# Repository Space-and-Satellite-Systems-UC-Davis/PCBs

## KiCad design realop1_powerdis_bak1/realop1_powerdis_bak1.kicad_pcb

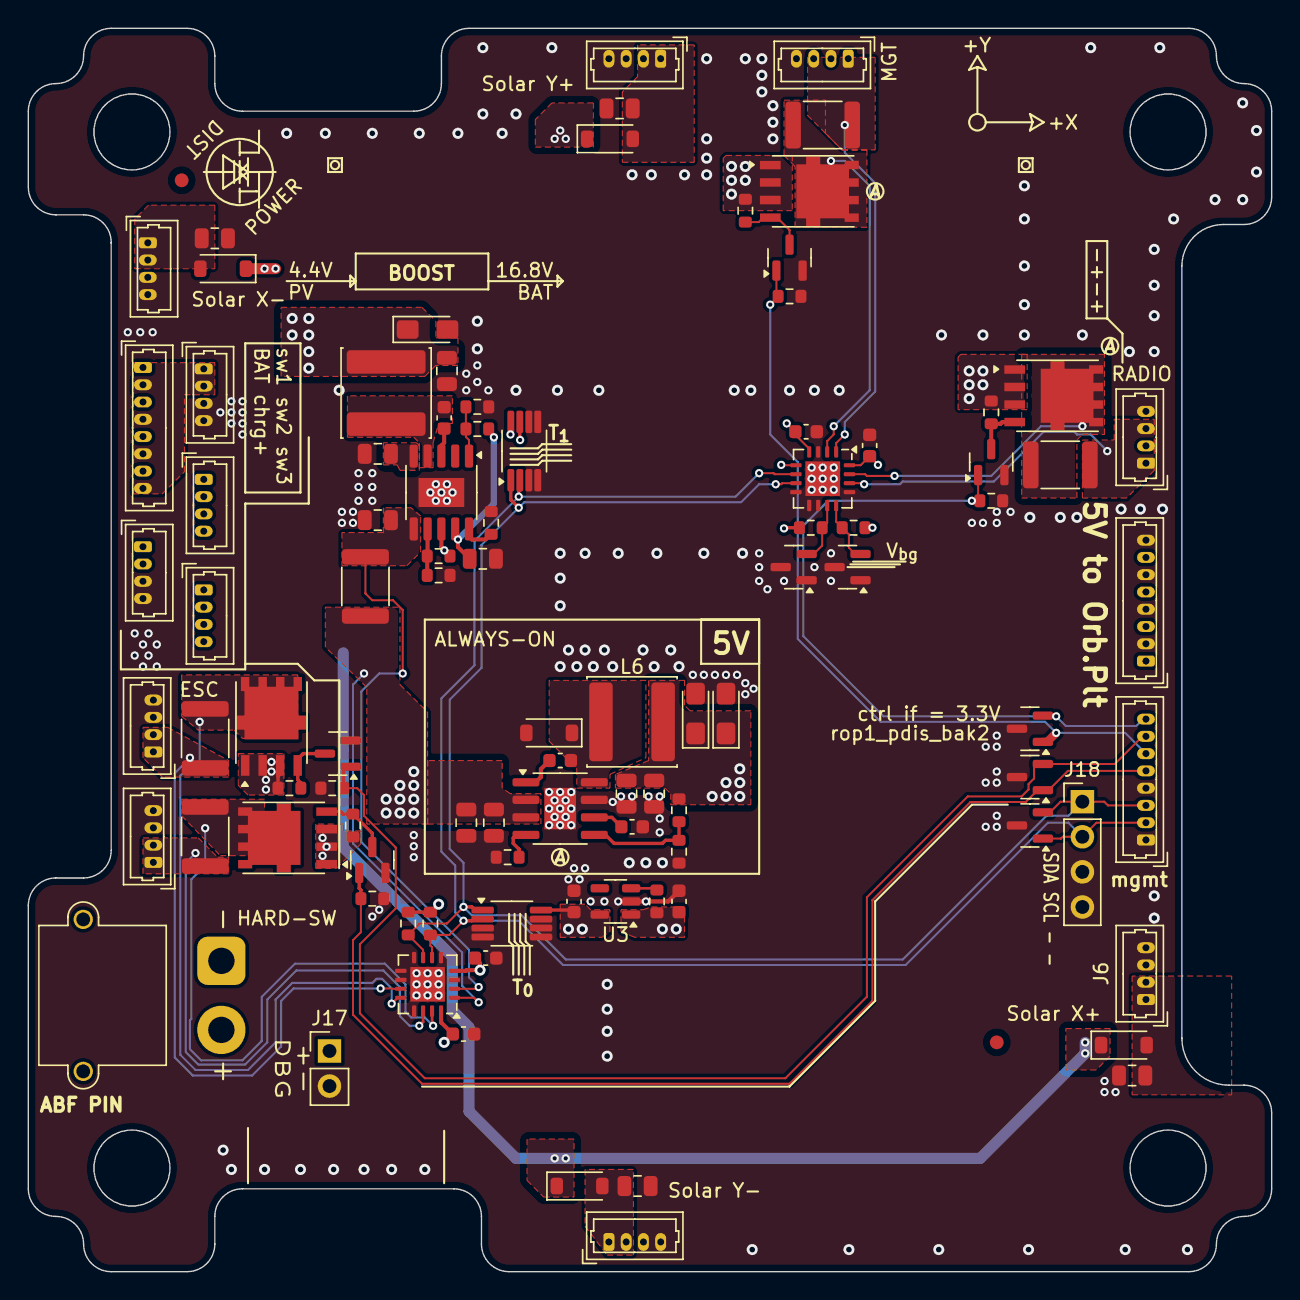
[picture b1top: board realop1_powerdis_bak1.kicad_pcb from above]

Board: 4 copper layers, 90.0 x 90.0 mm, 97 parts (0 on the bottom side), 47 nets.

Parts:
C1, C2, C3, C4, C14, C15, C16, C17, C25, C26, C29, C30: 10uF; C_0805_2012Metric
C5, C6, C18: 47uF A; CP_EIA-3216-18_Kemet-A_Pad1.58x1.35mm_HandSolder
C7, C8, C9, C10, C11, C12, C13, C28: 1uF; C_0603_1608Metric
C27: 10nF; C_0603_1608Metric
D1, D2, D3, D4, D5: 1n5819hw; D_SOD-123
D6, D7, D8: SM712_SOT23; SOT-23
FID1, FID2: Fiducial; Fiducial_1mm_Mask2mm
J1: mnt_fltctrl; Molex_PicoBlade_53047-0810_1x08_P1.25mm_Vertical
J2, J4, J5, J6, J7, J12, J15, J16: picoblade_1x4; Molex_PicoBlade_53047-0410_1x04_P1.25mm_Vertical
J3: Conn_01x08_MountingPin; Molex_PicoBlade_53047-0810_1x08_P1.25mm_Vertical
J8: bsw1; Molex_PicoBlade_53047-0410_1x04_P1.25mm_Vertical
J9: bsw2; Molex_PicoBlade_53047-0410_1x04_P1.25mm_Vertical
J10: bsw3; Molex_PicoBlade_53047-0410_1x04_P1.25mm_Vertical
J11: ground_charge; Molex_PicoBlade_53047-0410_1x04_P1.25mm_Vertical
J13: mgmt_if; Molex_PicoBlade_53047-0810_1x08_P1.25mm_Vertical
J14: xt30_2x; AMASS_XT30PW-M_1x02_P2.50mm_Horizontal
J17: test_DNP; PinHeader_1x02_P2.54mm_Vertical
J18: Conn_01x04; PinHeader_1x04_P2.54mm_Vertical
L1, L6: 10uH; L_APV_ANR6020
Q1, Q2, Q5, Q7: 2N7002E; SOT-23
Q3, Q4, Q6, Q8: SQJ479EP; PowerPak-SO8-EP-Vishay
Q9, Q10: MMBT3906; SOT-23
R1, R5, R7, R10, R24: 20mili; R_1812_4532Metric
R2, R3, R4, R6, R8, R9, R18, R19: 1k; R_0603_1608Metric
R11, R13, R21, R23, R25: 100k; R_0603_1608Metric
R12, R15, R16: 22k; R_0603_1608Metric
R14: 115k; R_0603_1608Metric
R17: 33k; R_0603_1608Metric
R20: 10k; R_0603_1608Metric
R22: 5.1k; R_0603_1608Metric
R26: 1meg; R_0603_1608Metric
U1: AP64350 / AP64352Q; SOIC-8-1EP_3.9x4.9mm_P1.27mm_EP2.29x3mm
U2, U4: INA3221; QFN-16-1EP_4x4mm_P0.65mm_EP2.5x2.5mm
U3: LP5907MFX-3.3; SOT-23-5
U5: LGS5524; SSOP-10-1EP_3.9x4.9mm_P1mm_EP2.1x3.3mm
U6, U7: TMP1075DGK; VSSOP-8_3x3mm_P0.65mm

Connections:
/5V_ALWAYS_ON+: C5.1, C6.1, C9.2, C29.2, C30.2, J1.1, J1.3, J1.5, J1.7, L6.2, R11.2, R14.1, U3.1 (IN)
/ICHRG_S+: C16.2, R24.2, U2.2 (IN+3), U5.6 (BAT)
/PV1_CHin: C1.2, D5.2 (A), J7.1, J7.2
/PV_BATO+: C15.2, C18.1, D1.1 (K), D2.1 (K), D3.1 (K), D5.1 (K), L1.1, R17.1, U5.8 (VIN)
/SCS_0+: Q3.5 (D), R5.1, U2.12 (IN+1)
/SCS_0-: J2.1, J2.2, R5.2, U2.11 (IN-1)
/SCS_1+: Q4.5 (D), R1.1, U4.2 (IN+3)
/SCS_1-: J12.1, J12.3, R1.2, U4.1 (IN-3)
/SCS_2+: Q6.5 (D), R7.1, U2.15 (IN+2)
/SCS_2-: J15.1, J15.2, R7.2, U2.14 (IN-2)
/SCS_3+: Q8.5 (D), R10.1, U4.15 (IN+2)
/SCS_3-: J16.1, J16.3, R10.2, U4.14 (IN-2)
/bc_v+: C17.2, R23.2, U5.9 (VCC)
/bgtemp+: Q9.2 (E), R25.2, U4.12 (IN+1)
/bgtemp-: Q10.2 (E), R26.2, U4.11 (IN-1)
/mgmt_scl: D6.1 (A1), J13.2, J18.2, R16.2, U2.6 (SCL), U4.6 (SCL), U6.2 (SCL), U7.2 (SCL)
/mgmt_sda: D6.2 (A2), J13.3, J18.1, R12.2, U2.7 (SDA), U4.7 (SDA), U6.1 (SDA), U7.1 (SDA)
/pwr0_en: D7.2 (A2), J13.7, Q2.1 (G), R19.2
/pwr1_en: D8.1 (A1), J13.6, Q1.1 (G), R4.2
/pwr2_en: D7.1 (A1), J13.5, Q5.1 (G), R2.2
/pwr3_en: D8.2 (A2), J13.8, Q7.1 (G), R8.2
BATPACK_V+: C25.2, C26.2, J14.2, J17.1, Q3.1 (S), Q3.2 (S), Q3.3 (S), Q4.1 (S), Q4.2 (S), Q4.3 (S), Q6.1 (S), Q6.2 (S), Q6.3 (S), Q8.1 (S), Q8.2 (S), Q8.3 (S), R3.1, R6.1, R9.1, R18.1, R24.1, U1.2 (VIN), U1.3 (EN), U2.1 (IN-3)
GND: C1.1, C2.1, C3.1, C4.1, C5.2, C6.2, C7.1, C8.1, C9.1, C10.1, C11.1, C12.1, C14.1, C15.1, C16.1, C17.1, C18.2, C25.1, C26.1, C27.1, C29.1, C30.1, D4.2 (A), D6.3 (common), D7.3 (common), D8.3 (common), J1.2, J1.4, J1.6, J1.8, J2.3, J2.4, J4.3, J4.4, J5.3, J5.4, J6.3, J6.4, J7.3, J7.4, J8.3, J8.4, J11.3, J11.4, J12.2, J12.4, J13.1, J13.4, J15.3, J15.4, J16.2, J16.4, J17.2, J18.3, J18.4, Q1.2 (S), Q2.2 (S), Q5.2 (S), Q7.2 (S), Q9.1 (B), Q9.3 (C), Q10.1 (B), Q10.3 (C), R2.1, R4.1, R8.1, R13.1, R15.2, R19.1, R20.2, R21.1, R22.1, U1.7 (GND), U1.9 (EPAD), U2.3 (GND), U2.5 (A0), U2.8 (WARNING), U2.9 (CRITICAL), U2.10 (PV), U2.13 (TC), U2.17 (EP), U3.2 (GND), U4.3 (GND), U4.8 (WARNING), U4.9 (CRITICAL), U4.10 (PV), U4.13 (TC), U4.17 (EP), U5.11 (EP), U6.3 (ALERT), U6.4 (GND), U6.5 (A2), U6.6 (A1), U6.7 (A0), U7.3 (ALERT), U7.4 (GND), U7.5 (A2), U7.6 (A1)
unnamed: C2.2, D1.2 (A), J4.1, J4.2
unnamed: C3.2, D2.2 (A), J5.1, J5.2
unnamed: C4.2, D3.2 (A), J6.1, J6.2
unnamed: C28.1, D4.1 (K), L6.1, U1.8 (LX)
unnamed: J3.2, J3.4, J3.6, J3.8, J8.1, J8.2
unnamed: J9.3, J9.4, J10.1, J10.2
unnamed: J10.3, J10.4, J14.1
unnamed: J3.1, J3.3, J3.5, J3.7, J9.1, J9.2, J11.1, J11.2
unnamed: Q1.3 (D), Q4.4 (G), R6.2
unnamed: Q2.3 (D), Q3.4 (G), R18.2
unnamed: Q5.3 (D), Q6.4 (G), R3.2
unnamed: Q7.3 (D), Q8.4 (G), R9.2
unnamed: C28.2, U1.1 (BOOT)
unnamed: C27.2, U1.6 (COMP)
unnamed: R14.2, R15.1, U1.5 (FB)
unnamed: R13.2, U1.4 (RT/CLK)
unnamed: R11.1, U3.3 (EN)
unnamed: C13.1, U5.3 (BST)
unnamed: R21.2, R23.1, U5.1 (EN/NTC)
unnamed: R22.2, U5.10 (ISET)
unnamed: C13.2, L1.2, U5.4 (SW)
unnamed: R17.2, R20.1, U5.7 (VHOLD)
unnamed: C14.2, U5.5 (VOUT)
ls3v+: C7.2, C8.2, C10.2, C11.2, C12.2, R12.1, R16.1, R25.1, R26.1, U2.4 (VS), U2.16 (VPU), U3.5 (OUT), U4.4 (VS), U4.5 (A0), U4.16 (VPU), U6.8 (V+), U7.7 (A0), U7.8 (V+)

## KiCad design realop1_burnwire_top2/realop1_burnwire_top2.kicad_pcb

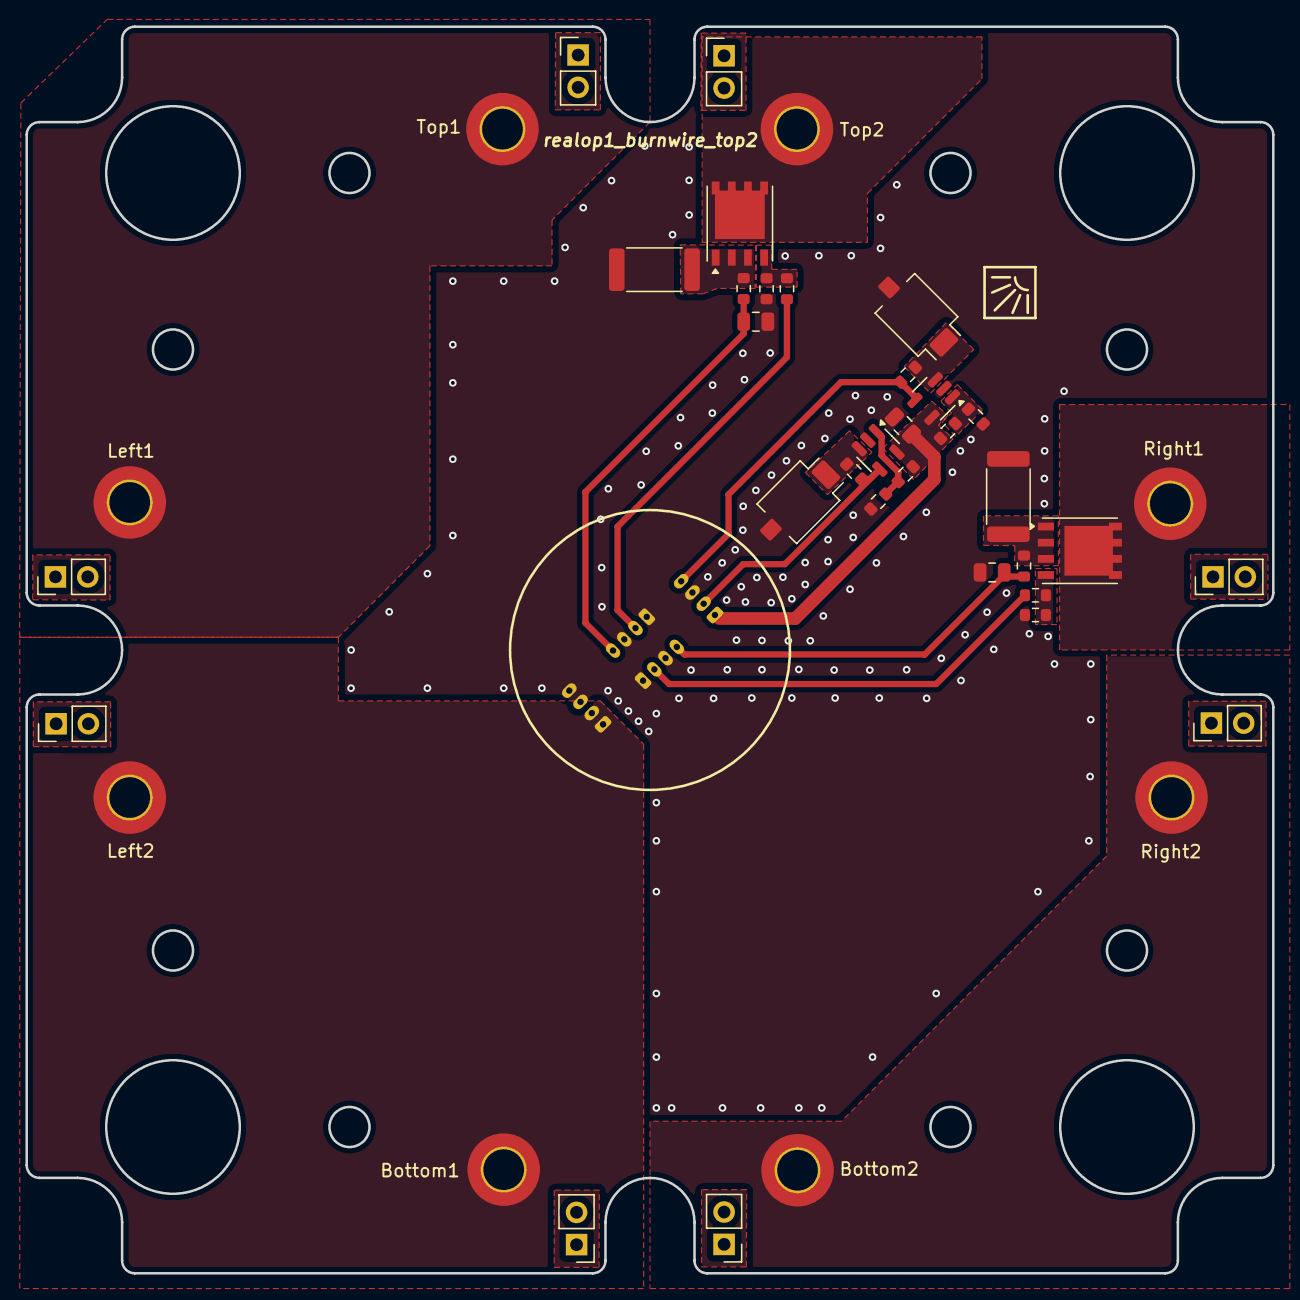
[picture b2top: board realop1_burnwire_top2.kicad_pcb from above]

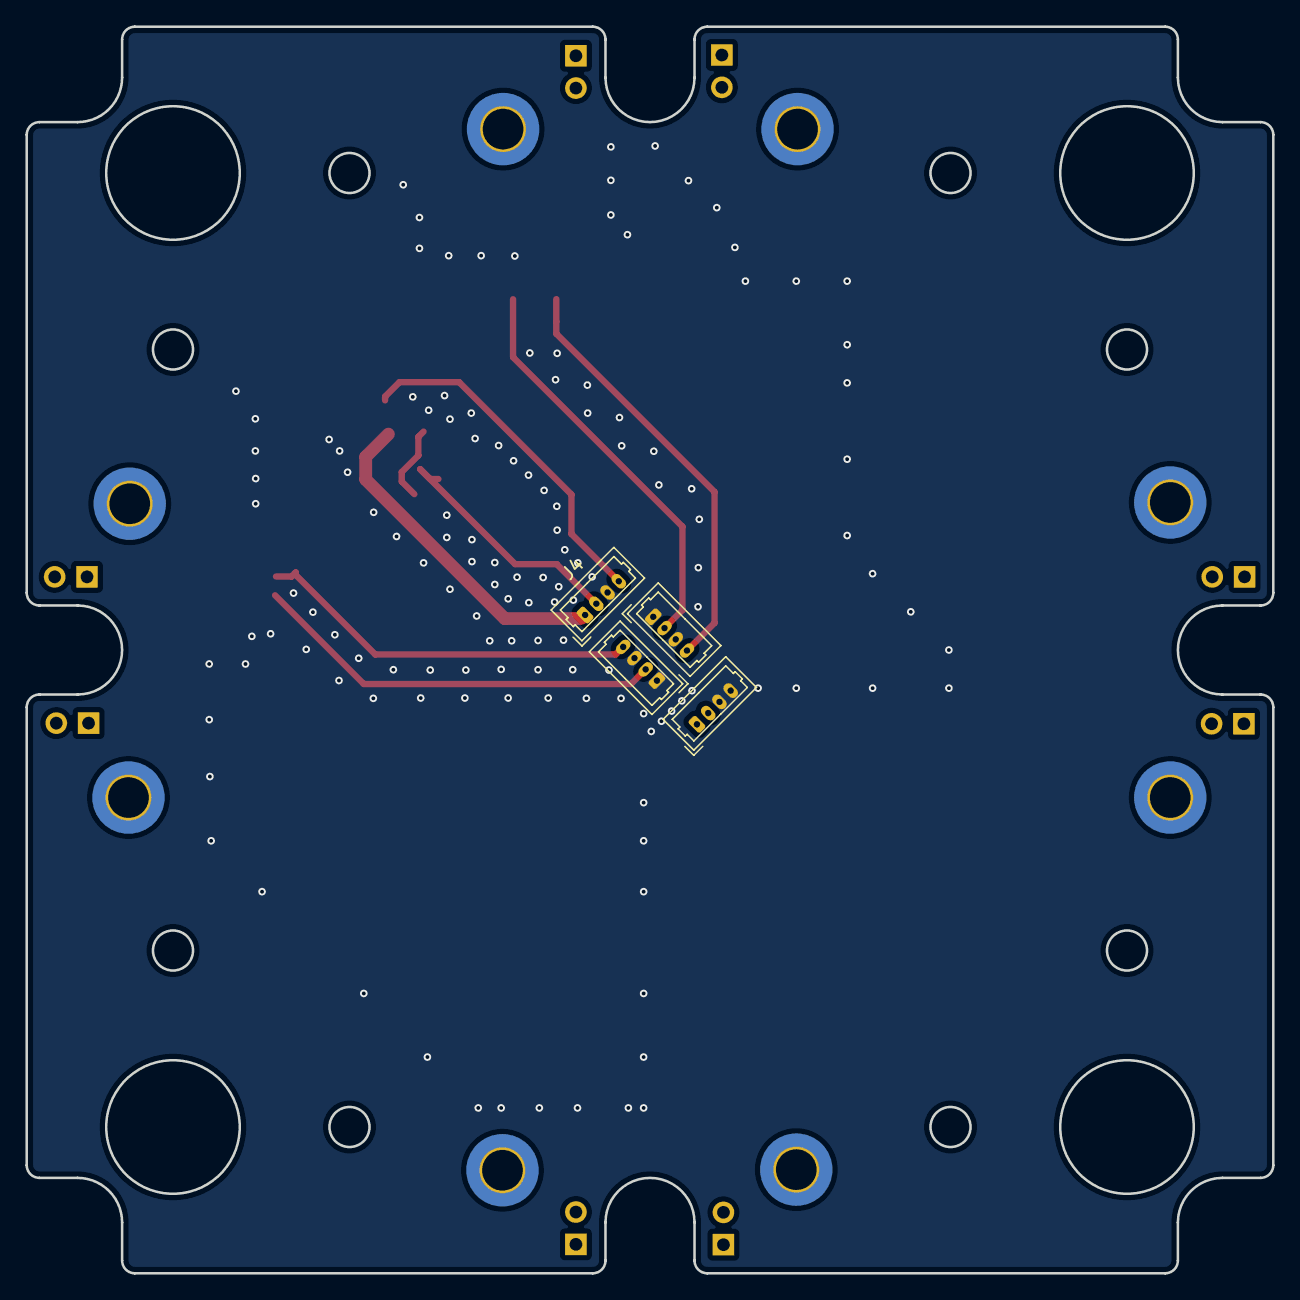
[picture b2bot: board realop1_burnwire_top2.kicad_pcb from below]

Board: 2 copper layers, 98.0 x 98.0 mm, 35 parts (4 on the bottom side), 21 nets.

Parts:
Bottom1, Bottom2: MountingHole_3.2mm_M3_ISO7380_Pad_TopBottom
C1, C2, C3: 10uF; C_0805_2012Metric
D1, D3: SFH2430; Osram_SFH2430
J1: BURNWIRE_SUPPLY; Molex_PicoBlade_53047-0410_1x04_P1.25mm_Vertical
J2: pyro0; Molex_PicoBlade_53047-0410_1x04_P1.25mm_Vertical
J3: pyro1; Molex_PicoBlade_53047-0410_1x04_P1.25mm_Vertical
J4: photodiode; Molex_PicoBlade_53047-0410_1x04_P1.25mm_Vertical
Left1, Left2: MountingHole_3.2mm_M3_ISO7380_Pad_TopBottom
Q1, Q2: BSC0702LS; PowerPAK_SO-8_Single
R3, R9, R13, R14, R17, R18: 100k; R_0603_1608Metric
R4, R11: 1; R_2512_6332Metric
R5, R7, R15, R16: 1k; R_0603_1608Metric
R6, R12: 10k; R_0603_1608Metric
Right1, Right2: MountingHole_3.2mm_M3_ISO7380_Pad_TopBottom
Top1, Top2: MountingHole_3.2mm_M3_ISO7380_Pad_TopBottom
U1, U2: LMV321; SOT-23-5

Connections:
+24V: Bottom1.1, J1.1, J1.2, Left2.1
/3v3_tia: C2.1, J4.1, R14.1, R17.1, U1.5 (V+), U2.5 (V+)
/pd_tia0: J4.2, R18.1, U1.4
/pd_tia1: J4.4, R3.1, U2.4
/pyro0_cs: C1.1, J2.4, R6.2
/pyro0_enable: J2.2, R5.1
/pyro1_cs: C3.1, J3.4, R12.2
/pyro1_enable: J3.2, R7.1
GND: C1.2, C2.2, C3.2, D1.2 (A), D3.2 (A), J1.3, J1.4, J2.1, J2.3, J3.1, J3.3, J4.3, R4.2, R9.2, R11.2, R13.1, R15.1, R16.1, U1.2 (V-), U2.2 (V-)
unnamed: D1.1 (K), R3.2, U2.3 (-)
unnamed: D3.1 (K), R18.2, U1.3 (-)
unnamed: Q1.5 (D), Top2.1
unnamed: Q1.4 (G), R5.2, R13.2
unnamed: Q1.1 (S), Q1.2 (S), Q1.3 (S), R4.1, R6.1
unnamed: Q2.5 (D), Right1.1
unnamed: Q2.4 (G), R7.2, R9.1
unnamed: Q2.1 (S), Q2.2 (S), Q2.3 (S), R11.1, R12.1
unnamed: Left1.1, Top1.1
unnamed: Bottom2.1, Right2.1
unnamed: R16.2, R17.2, U1.1 (+)
unnamed: R14.2, R15.2, U2.1 (+)

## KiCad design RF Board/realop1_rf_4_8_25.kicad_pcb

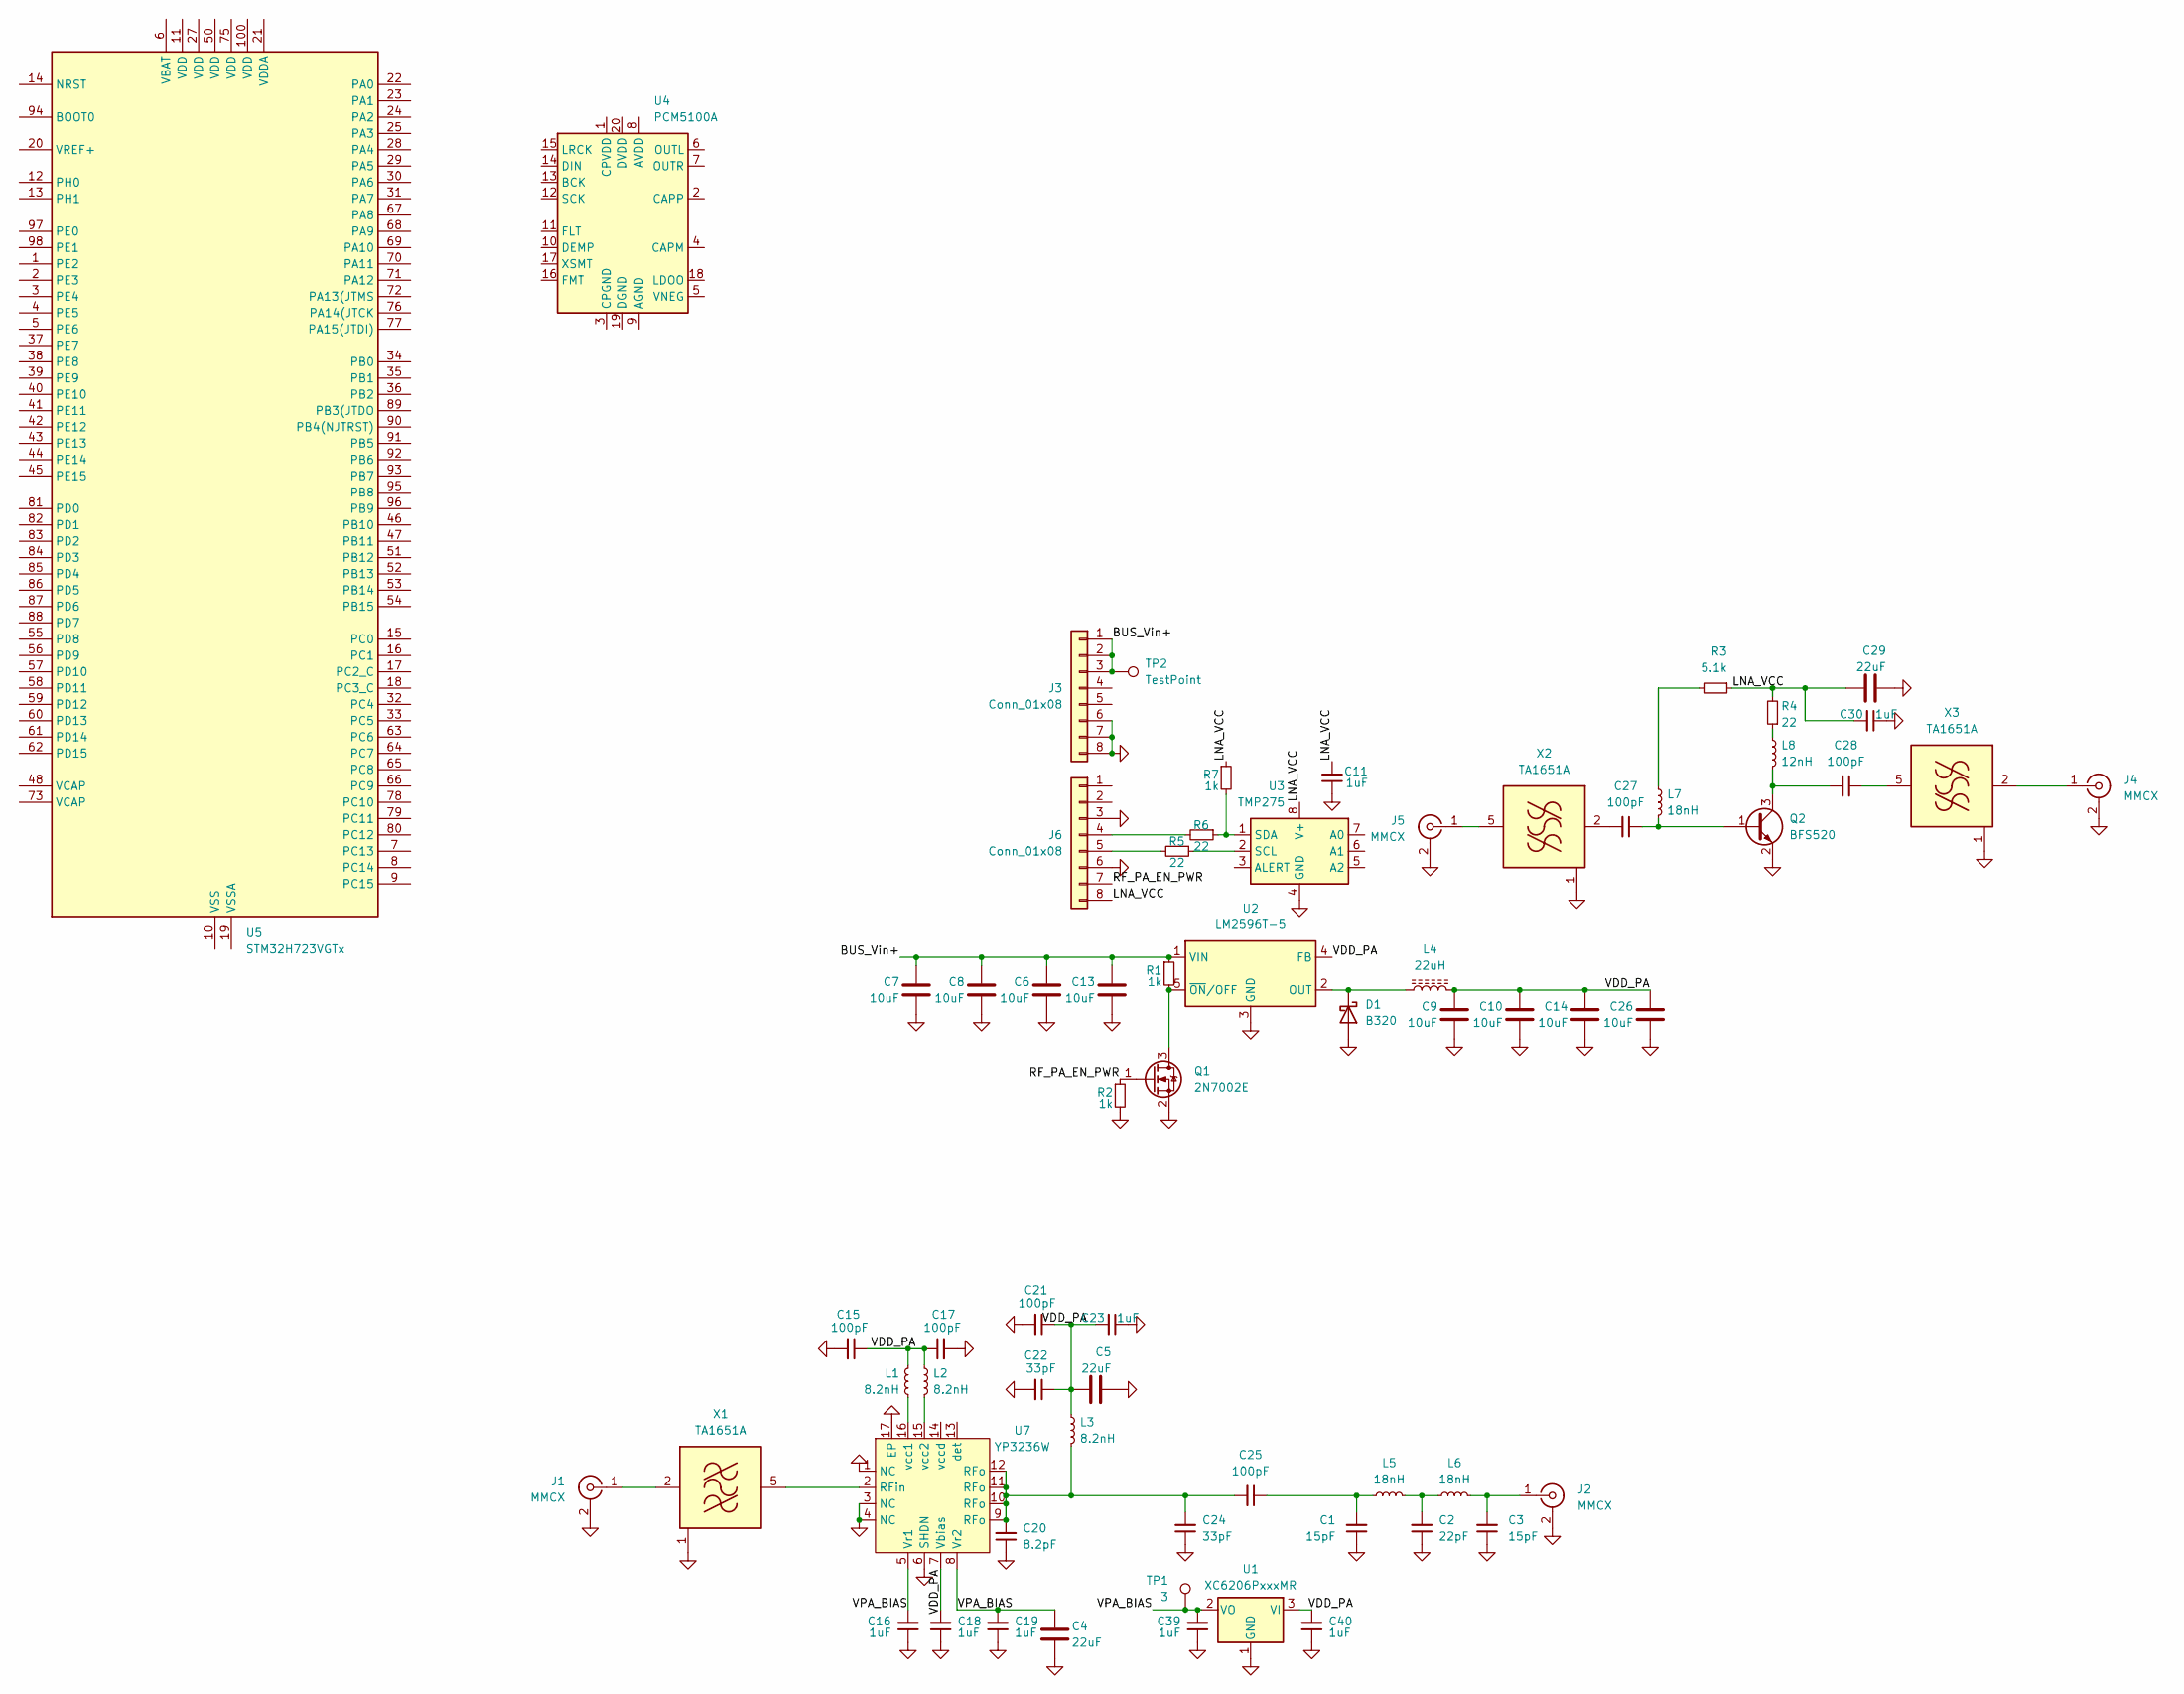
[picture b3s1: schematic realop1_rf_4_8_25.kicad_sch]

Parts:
C1, C3: 15pF; C_0402_1005Metric
C2: 22pF; C_0402_1005Metric
C4, C5, C29: 22uF; C_0805_2012Metric
C6, C7, C8, C9, C10, C13, C14, C26: 10uF; C_1210_3225Metric
C11, C16, C18, C19, C23, C30, C39, C40: 1uF; C_0603_1608Metric
C15, C17, C21: 100pF; C_0603_1608Metric
C20: 8.2pF; C_0402_1005Metric
C22: 33pF; C_0603_1608Metric
C24: 33pF; C_0402_1005Metric
C25, C27, C28: 100pF; C_0402_1005Metric
D1: B320; D_SMC
J1, J2, J4, J5: MMCX; rpMMCX_edge_1.6mmPCB
J3, J6: Conn_01x08; Molex_PicoBlade_53047-0810_1x08_P1.25mm_Vertical
L1, L2: 8.2nH; L_0603_1608Metric
L3: 8.2nH; L_1008_2520Metric
L4: 22uH; L_Changjiang_FXL1040
L5, L6, L7: 18nH; L_0603_1608Metric
L8: 12nH; L_0603_1608Metric
Q1: 2N7002E; SOT-23
Q2: BFS520; SOT-323-GDsp
R1, R2, R7: 1k; R_0603_1608Metric
R3: 5.1k; R_0603_1608Metric
R4, R5, R6: 22; R_0603_1608Metric
TP1: 3; TestPoint_Pad_D1.0mm
TP2: TestPoint; TestPoint_Pad_4.0x4.0mm
U1: XC6206PxxxMR; SOT-23-3
U2: LM2596T-5; TO220-5-Flatmnt
U3: TMP275; VSSOP-8_3x3mm_P0.65mm
U4: PCM5100A; TSSOP-20_4.4x6.5mm_P0.65mm
U5: STM32H723VGTx; LQFP-100_14x14mm_P0.5mm
U7: YP3236W; QFN-16_4x4_P0.65mm_RF
X1, X2, X3: TA1651A; Filter_SAW_Epcos_DCC6C_3x3mm

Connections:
/BUS_Vin+: C6.1, C7.1, C8.1, C13.1, J3.1, J3.2, J3.3, R1.1, TP2.1, U2.1 (VIN)
/LNA_VCC: C11.2, C29.1, C30.2, J6.8, R3.1, R4.2, R7.1, U3.8 (V+)
/RF_PA_EN_PWR: J6.7, Q1.1 (G), R2.1
/VDD_PA: C5.1, C9.1, C10.1, C14.1, C15.1, C17.1, C18.2, C21.1, C22.1, C23.2, C26.1, C40.2, L1.1, L2.1, L3.1, L4.2, U1.3 (VI), U2.4 (FB), U7.7 (Vbias)
/VPA_BIAS: C4.1, C16.2, C19.2, C39.2, TP1.1, U1.2 (VO), U7.5 (Vr1), U7.8 (Vr2)
GND: C1.1, C2.1, C3.1, C4.2, C5.2, C6.2, C7.2, C8.2, C9.2, C10.2, C11.1, C13.2, C14.2, C15.2, C16.1, C17.2, C18.1, C19.1, C20.1, C21.2, C22.2, C23.1, C24.1, C26.2, C29.2, C30.1, C39.1, C40.1, D1.2 (A), J1.2 (Ext), J2.2 (Ext), J3.6, J3.7, J3.8, J4.2 (Ext), J5.2 (Ext), J6.3, J6.6, Q1.2 (S), Q2.2 (E), R2.2, U1.1 (GND), U2.3 (GND), U3.4 (GND), U7.1 (NC), U7.3 (NC), U7.4 (NC), U7.6 (SHDN), U7.17 (EP), X1.1 (GND), X1.3 (GND), X1.4 (GND), X1.6 (GND), X2.1 (GND), X2.3 (GND), X2.4 (GND), X2.6 (GND), X3.1 (GND), X3.3 (GND), X3.4 (GND), X3.6 (GND)
unnamed: C1.2, C25.1, L5.1
unnamed: C2.2, L5.2, L6.1
unnamed: C20.2, C24.2, C25.2, L3.2, U7.9 (RFo), U7.10 (RFo), U7.11 (RFo), U7.12 (RFo)
unnamed: D1.1 (K), L4.1, U2.2 (OUT)
unnamed: J1.1 (In), X1.2 (IN)
unnamed: C3.2, J2.1 (In), L6.2
unnamed: J4.1 (In), X3.2 (IN)
unnamed: J5.1 (In), X2.5 (OUT)
unnamed: J6.4, R6.2
unnamed: J6.5, R5.2
unnamed: L7.1, R3.2
unnamed: L8.1, R4.1
unnamed: Q1.3 (D), R1.2, U2.5 (~ON/OFF)
unnamed: C27.1, L7.2, Q2.1 (B)
unnamed: C28.2, L8.2, Q2.3 (C)
unnamed: R5.1, U3.2 (SCL)
unnamed: R6.1, R7.2, U3.1 (SDA)
unnamed: U5.10 (VSS), U5.26 (VSS), U5.49 (VSS), U5.74 (VSS), U5.99 (VSS)
unnamed: U7.2 (RFin), X1.5 (OUT)
unnamed: L1.2, U7.16 (vcc1)
unnamed: L2.2, U7.15 (vcc2)
unnamed: C27.2, X2.2 (IN)
unnamed: C28.1, X3.5 (OUT)

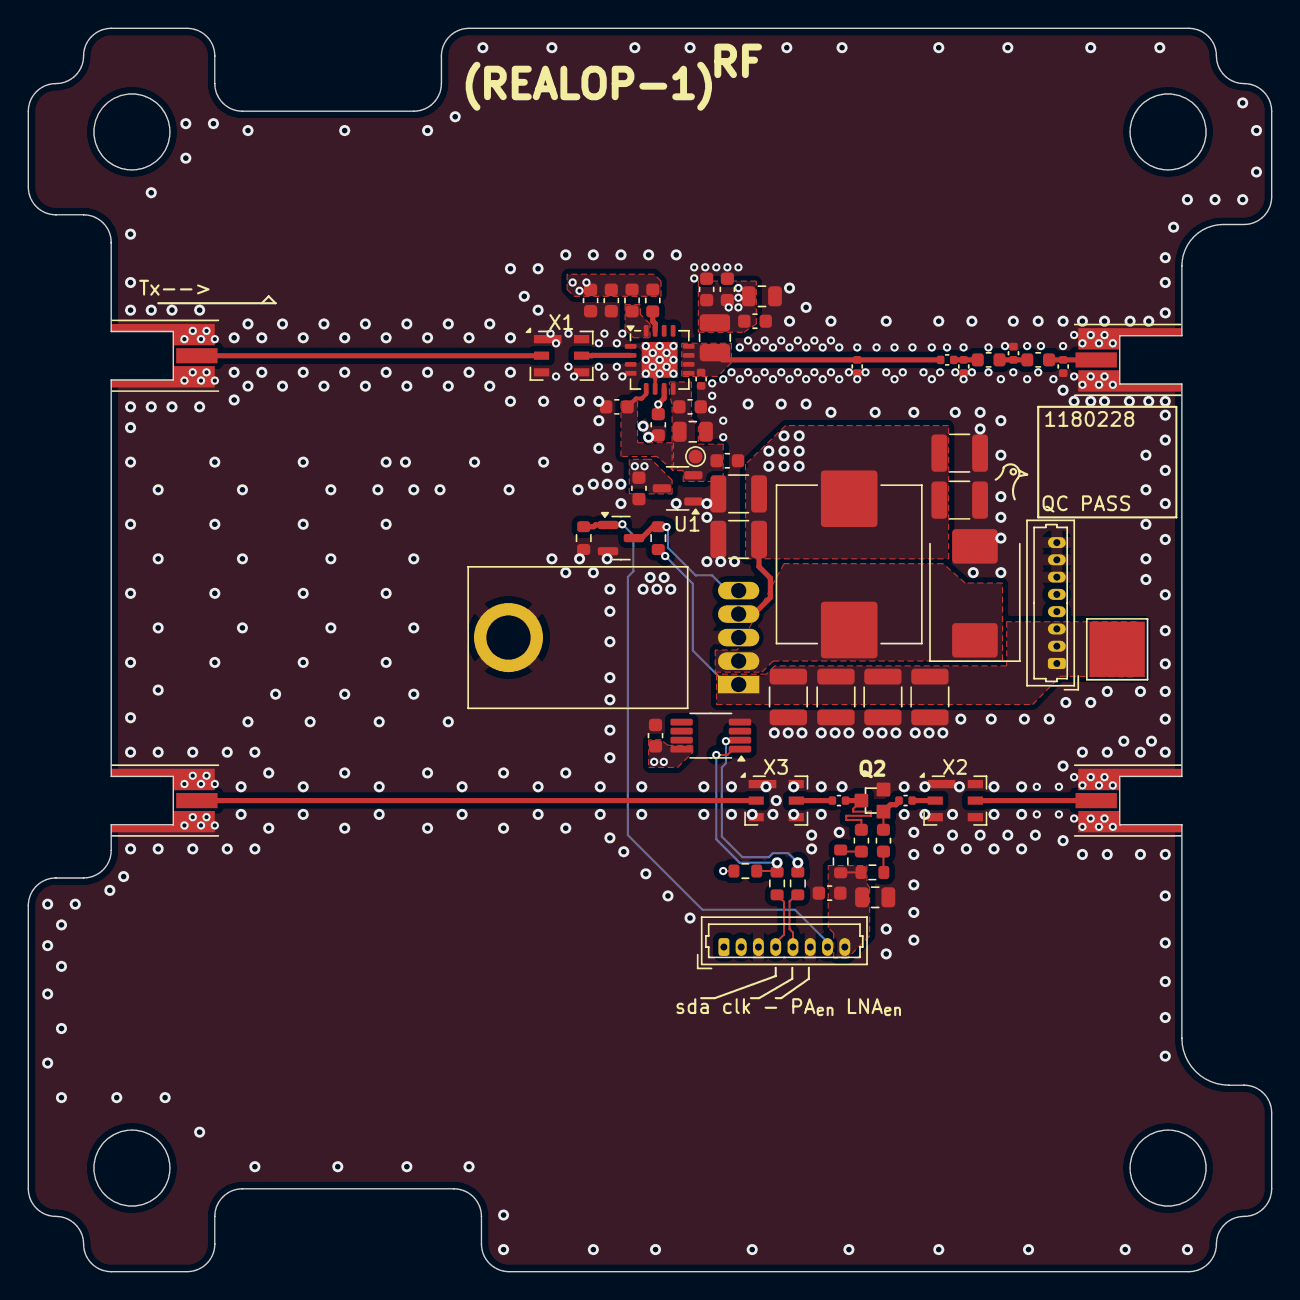
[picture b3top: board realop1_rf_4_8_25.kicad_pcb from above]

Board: 4 copper layers, 90.0 x 90.0 mm, 64 parts (0 on the bottom side), 28 nets.

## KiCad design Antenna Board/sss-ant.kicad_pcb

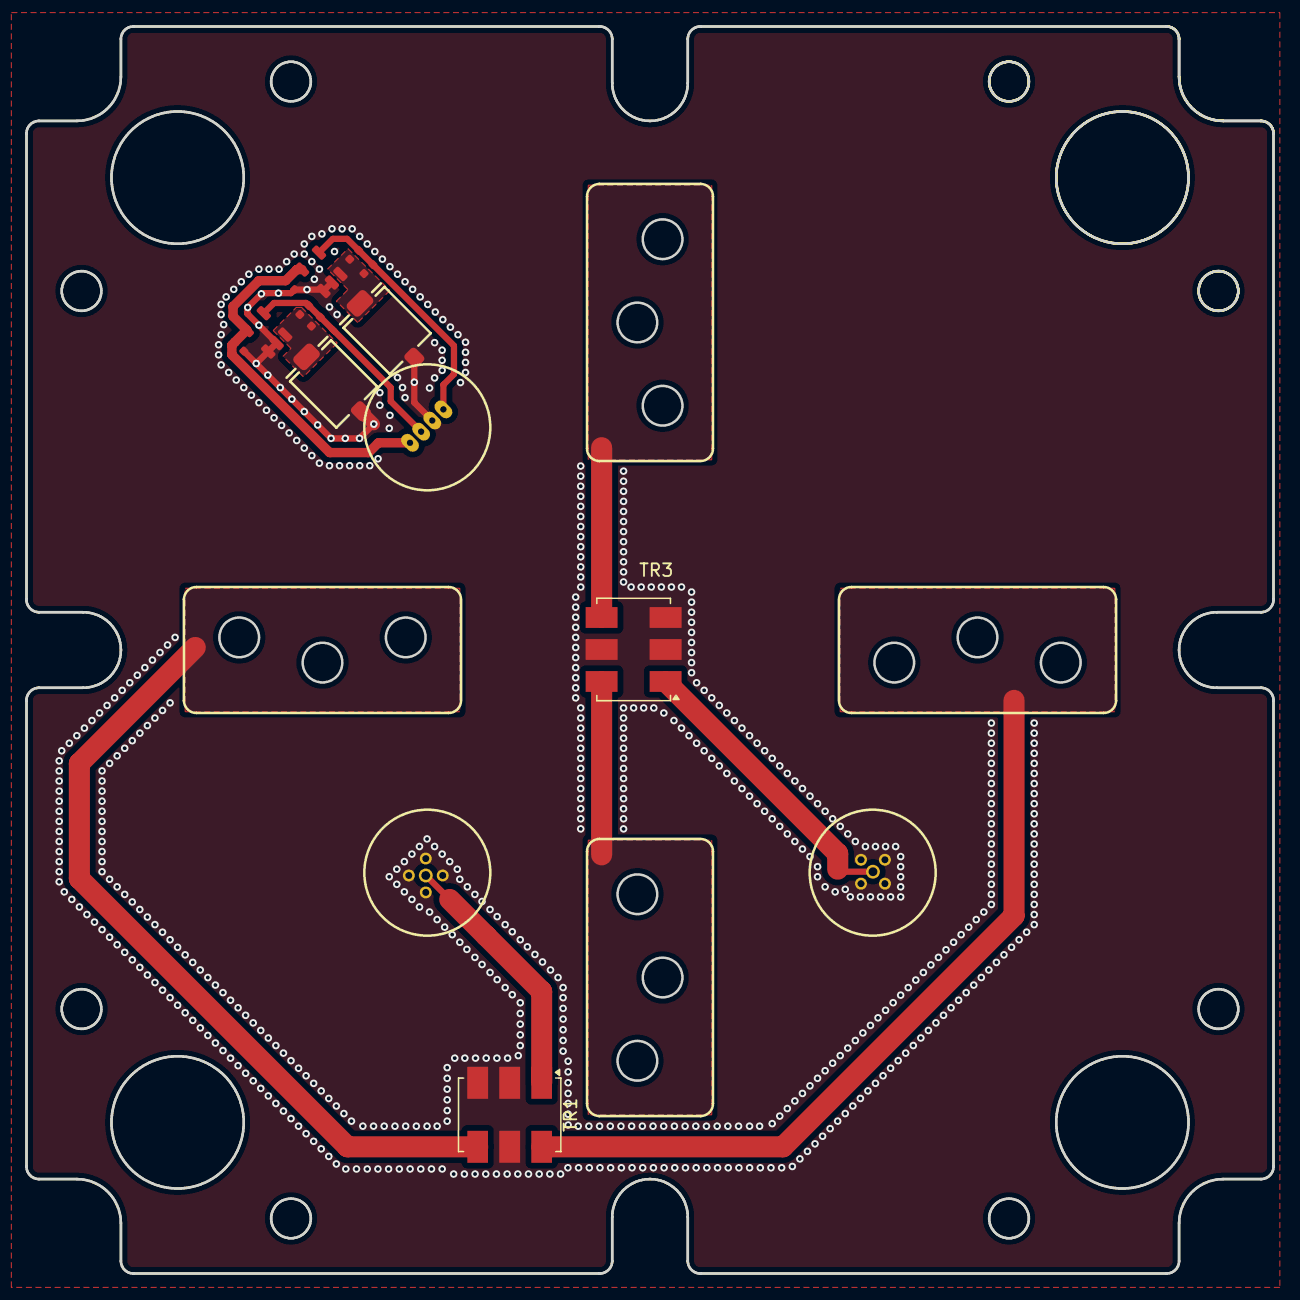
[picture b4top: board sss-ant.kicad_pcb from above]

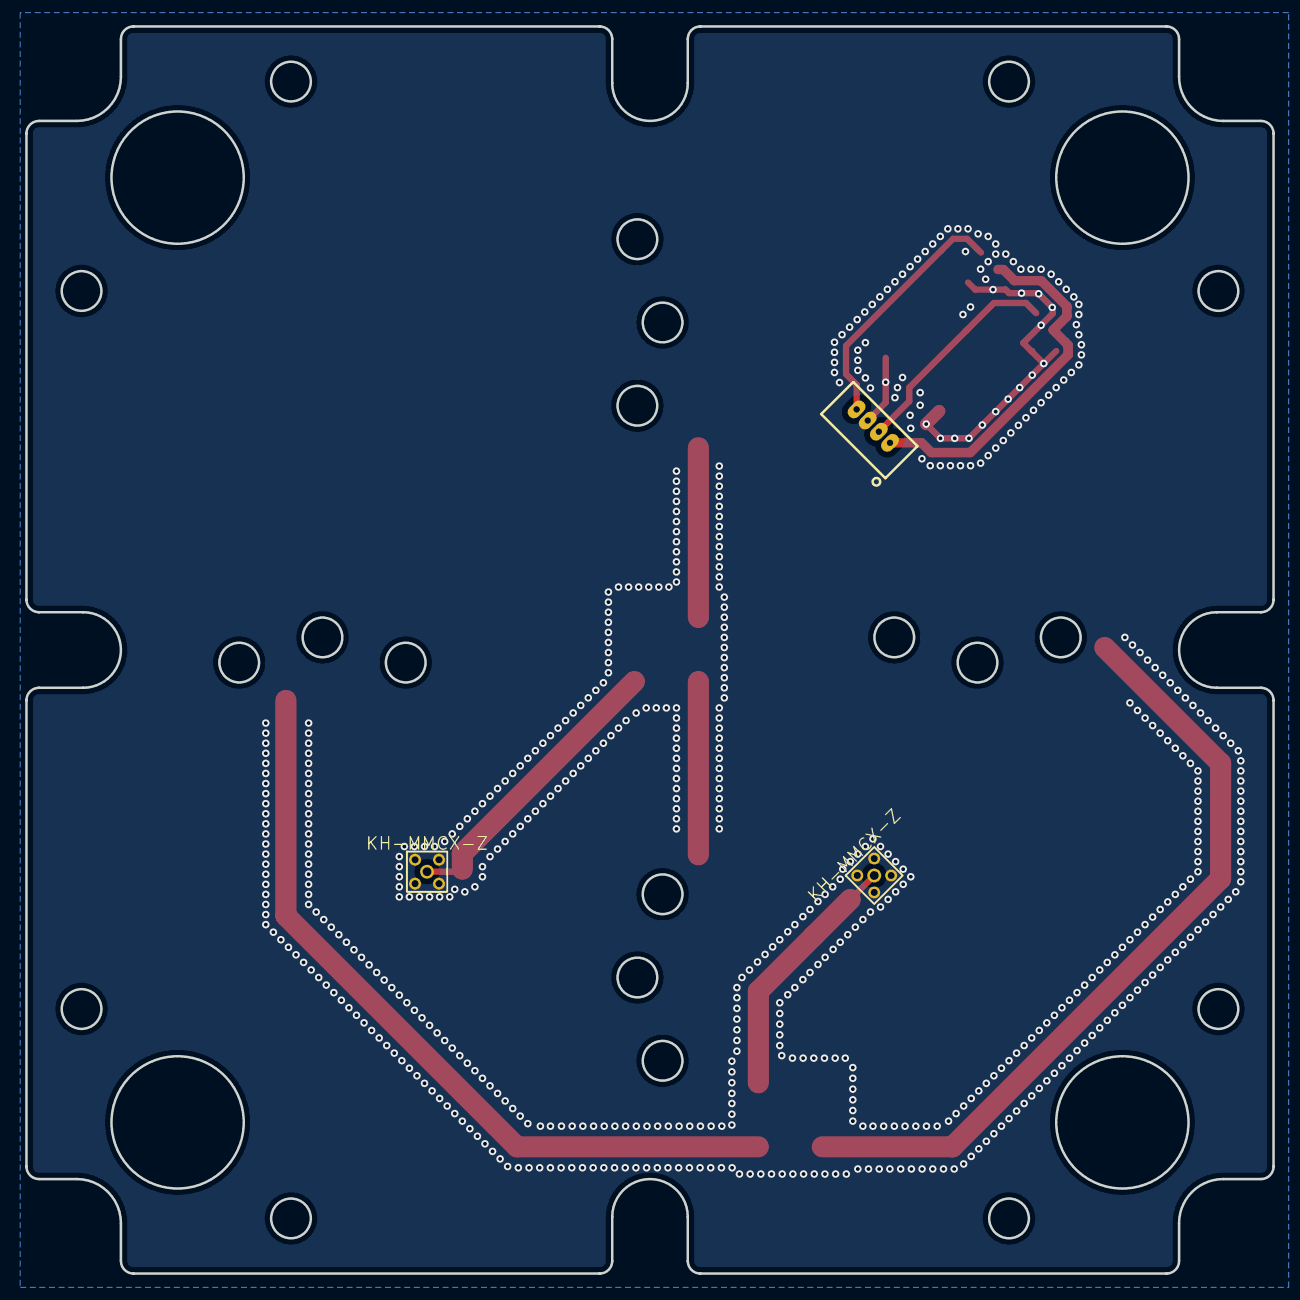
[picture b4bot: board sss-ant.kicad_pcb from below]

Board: 2 copper layers, 99.0 x 99.0 mm, 15 parts (3 on the bottom side), 8 nets.

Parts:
C1, C3: 100nF; Yu-C-0402-mil
C2, C4: 100pF; Yu-C-0402-mil
D1, D2: SFH2430; Yu-D-PD-Osram-SFH2430
J5: Yu-Molex-Picoblade-530470410-1x04-1.25-THM-V
KH-MMCX-Z: Shenzhen Kinghelm Elec KH-MMCX-Z
KH-MMCX-Z#2: Shenzhen Kinghelm Elec KH-MMCX-Z
R1, R2: 10k; Yu-R-0402-mil
TR1, TR3: ADTL1-12; Mini-Circuits_CD542_H2.84mm
U1, U2: LMV321; Yu-SOT-23-5

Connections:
/pd0: C2.2, J5.2, R1.2, U1.4
/pd1: C4.2, J5.4, R2.2, U2.4
/v3v3: C1.1, C3.1, J5.1, U1.5 (V+), U2.5 (V+)
GND: C1.2, C3.2, D1.2 (A), D2.2 (A), J5.3, KH-MMCX-Z.0, KH-MMCX-Z#2.0, TR1.2, TR1.3, TR1.5, TR3.2, TR3.3, TR3.5, U1.1 (+), U1.2 (V-), U2.1 (+), U2.2 (V-)
unnamed: C2.1, D1.1 (K), R1.1, U1.3 (-)
unnamed: C4.1, D2.1 (K), R2.1, U2.3 (-)
unnamed: KH-MMCX-Z#2.1, TR3.1
unnamed: KH-MMCX-Z.1, TR1.1
